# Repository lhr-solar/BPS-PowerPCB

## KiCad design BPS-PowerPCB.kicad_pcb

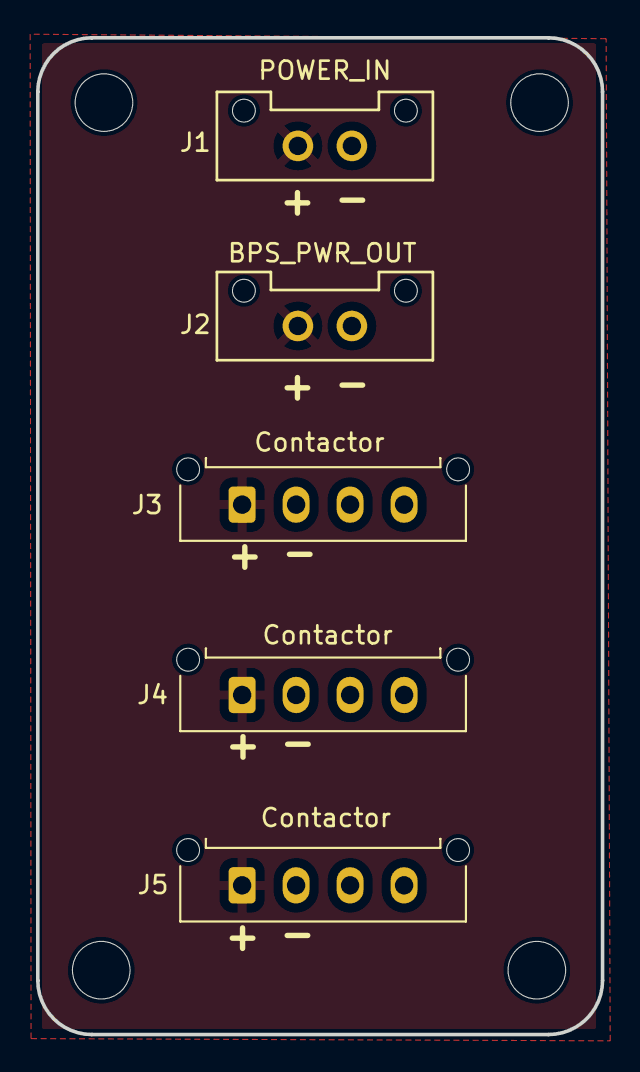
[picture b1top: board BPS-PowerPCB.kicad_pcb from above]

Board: 2 copper layers, 31.4 x 55.4 mm, 5 parts (0 on the bottom side), 2 nets, no tracks yet.

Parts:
J1: POWER_IN; Molex_MicroFit3.0_1x2xP3.00mm_PolarizingPeg_Vertical
J2: BPS_PWR_OUT; Molex_MicroFit3.0_1x2xP3.00mm_PolarizingPeg_Vertical
J3, J4, J5: Contactor; Molex_Micro-Fit_3.0_43650-0415_1x04_P3.00mm_Vertical

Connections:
+12V: J1.1, J2.1, J3.1, J4.1, J5.1
GND: J1.2, J2.2, J3.2, J4.2, J5.2

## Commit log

2024-10-16 done may need to add labels
